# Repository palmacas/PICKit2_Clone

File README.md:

# PICKit2 Clone

This is a DIY version (clone) of the well known Microchip's PICKit2 programmer, with an additional ZIF socket. The repository contains the editable EAGLE files and the scheme on PDF. In addition, the ZIF_Distribution folder contains images with the ICs and jumpers distribution on the ZIF socket depending on the PIC type.

---
More information:  
[PICKit 2 Clone Zócalo ZIF [Spanish]](https://palmacas.com/pickit-2-clone-zocalo-zif/)  
[Zócalo ZIF – PICKit 2 y PICKit 3 [Spanish]](https://palmacas.com/zocalo-zif-pickit-2-y-pickit-3/)  
[Distribución de Zócalo ZIF [Spanish]](https://palmacas.com/distribucion-zocalo-zif/)  
[PICKit 2 Clone ICSP [Spanish]](https://palmacas.com/pickit-2-clone-icsp/)

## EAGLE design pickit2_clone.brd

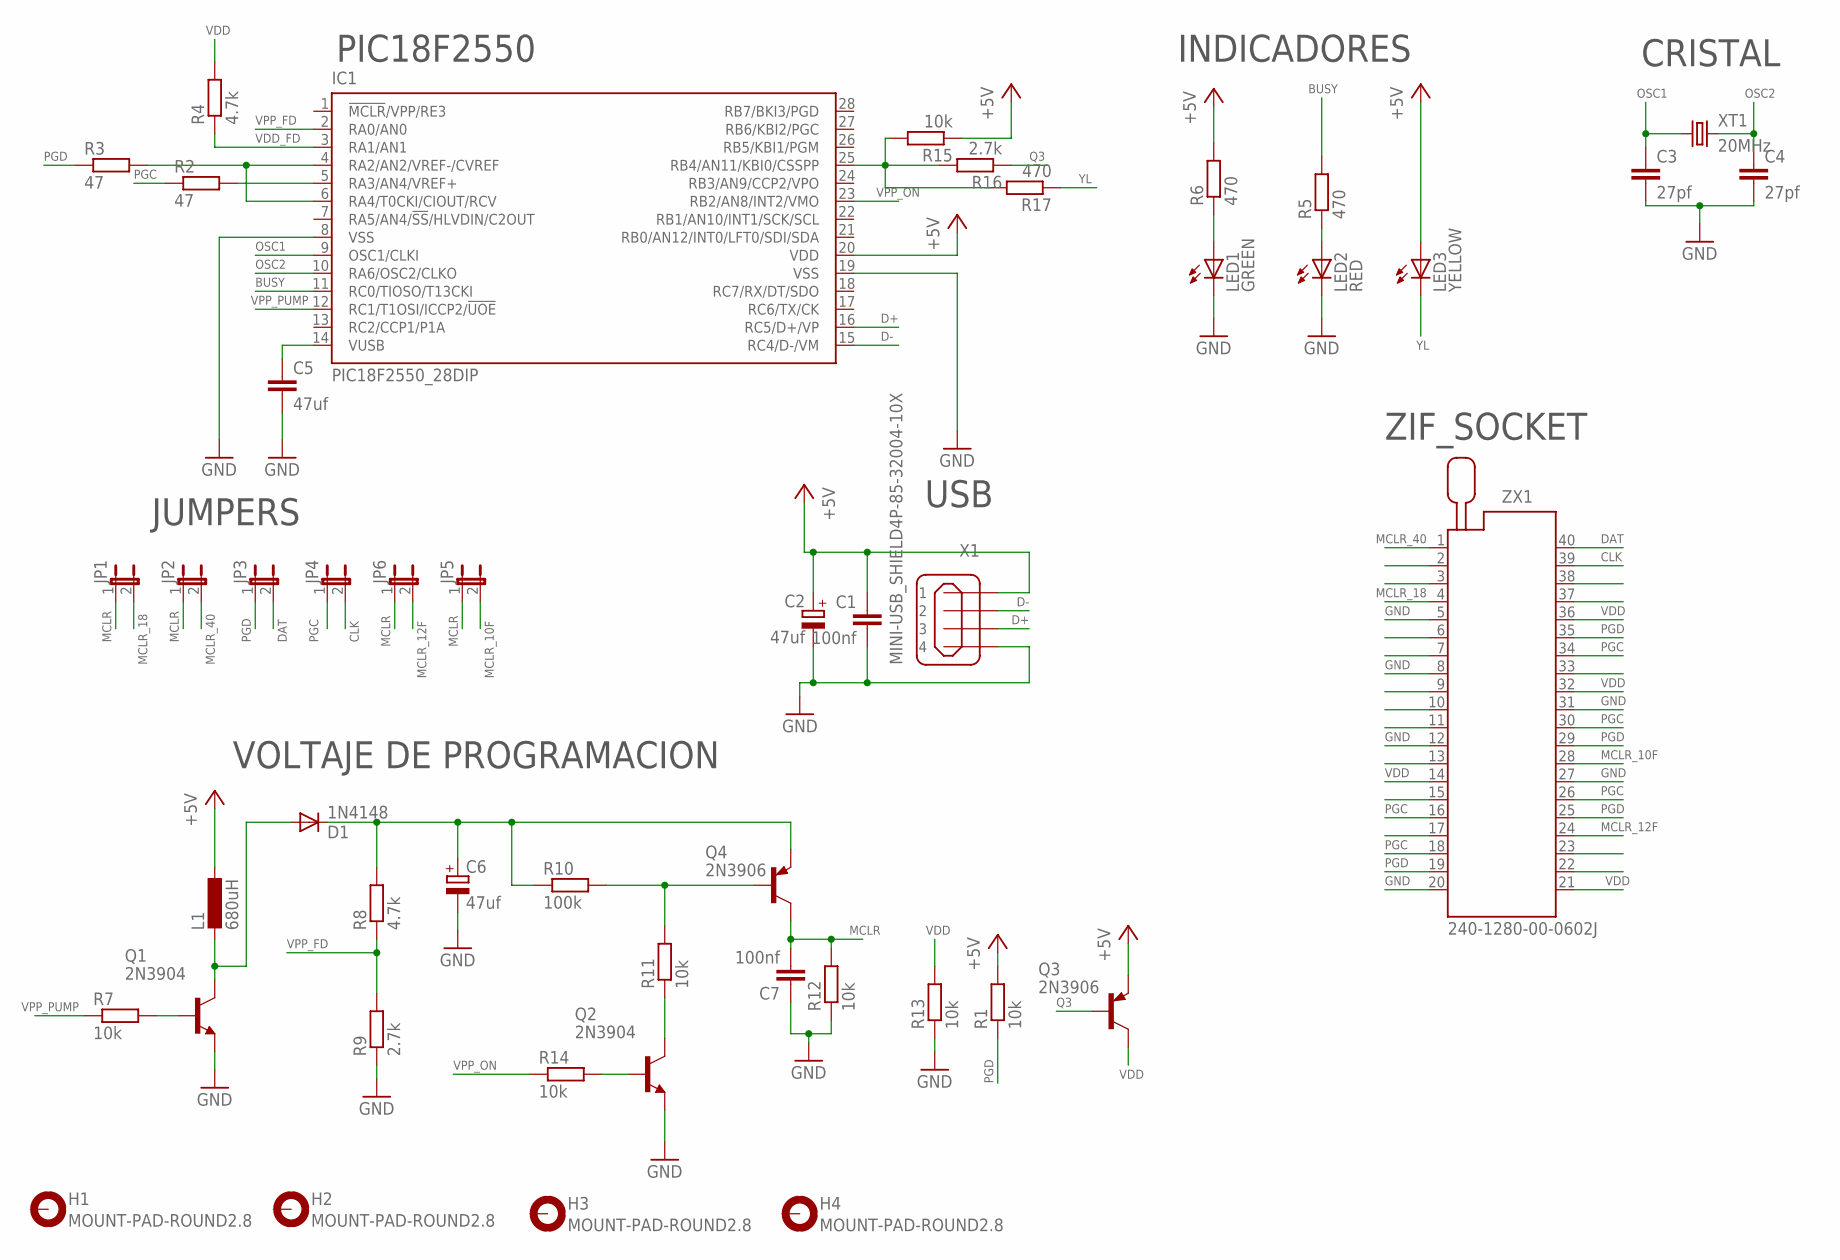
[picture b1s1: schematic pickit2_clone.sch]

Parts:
C1, C7: 100nf; C025-030X050
C2, C6: 47uf; E2-5
C3, C4: 27pf; C050-030X075
C5: 47uf; C050-030X075
D1: 1N4148; DO35-10
H1, H2, H3, H4: MOUNT-PAD-ROUND2.8; 2,8-PAD
IC1: PIC18F2550_28DIP; DIL28-3
JP1, JP2, JP3, JP4, JP5, JP6: JP1E; JP1
L1: 680uH; 0207/10
LED1: GREEN; LED5MM
LED2: RED; LED5MM
LED3: YELLOW; LED5MM
Q1, Q2: 2N3904; TO92-EBC
Q3, Q4: 2N3906; TO92-CBE
R1, R7, R11, R12, R13, R14, R15: 10k; 0207/7
R2, R3: 47; 0207/7
R4, R8: 4.7k; 0207/7
R5, R6, R17: 470; 0207/7
R9, R16: 2.7k; 0207/7
R10: 100k; 0207/7
X1: MINI-USB_SHIELD4P-85-32004-10X; 85-32004-10X
XT1: 20MHz; HC49/S
ZX1: 240-1280-00-0602J

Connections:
+5V: C1.1, C2.+, IC1.20 (VDD), L1.1, LED3.A, Q3.E, R1.2, R6.2, R15.1, X1.1
BUSY: IC1.11 (RC0/TIOSO/T13CKI), R5.2
CLK: JP4.2, ZX1.39
D+: IC1.16 (RC5/D+/VP), X1.3
D-: IC1.15 (RC4/D-/VM), X1.2
DAT: JP3.2, ZX1.40
GND: C1.2, C2.-, C3.2, C4.2, C5.2, C6.-, C7.1, IC1.8 (VSS), IC1.19 (VSS), LED1.K (C), LED2.K (C), Q1.E, Q2.E, R9.1, R12.1, R13.1, X1.4, ZX1.5, ZX1.8, ZX1.12, ZX1.20, ZX1.27, ZX1.31
MCLR: C7.2, JP1.1, JP2.1, JP5.1, JP6.1, Q4.C, R12.2
MCLR_10F: JP5.2, ZX1.28
MCLR_12F: JP6.2, ZX1.24
MCLR_18: JP1.2, ZX1.4
MCLR_40: JP2.2, ZX1.1
unnamed: C5.1, IC1.14 (VUSB)
unnamed: LED1.A, R6.1
unnamed: IC1.4 (RA2/AN2/VREF-/CVREF), IC1.6 (RA4/T0CKI/CIOUT/RCV), R3.2
unnamed: Q1.B, R7.2
unnamed: IC1.5 (RA3/AN4/VREF+), R2.2
unnamed: LED2.A, R5.1
unnamed: C6.+, D1.C, Q4.E, R8.2, R10.1
unnamed: Q4.B, R10.2, R11.2
unnamed: IC1.25 (RB4/AN11/KBI0/CSSPP), R15.2, R16.2, R17.2
unnamed: Q2.C, R11.1
unnamed: Q2.B, R14.2
unnamed: D1.A, L1.2, Q1.C
OSC1: C3.1, IC1.9 (OSC1/CLKI), XT1.1
OSC2: C4.1, IC1.10 (RA6/OSC2/CLKO), XT1.2
PGC: JP4.1, R2.1, ZX1.16, ZX1.18, ZX1.26, ZX1.30, ZX1.34
PGD: JP3.1, R1.1, R3.1, ZX1.19, ZX1.25, ZX1.29, ZX1.35
Q3: Q3.B, R16.1
VDD: Q3.C, R4.2, R13.2, ZX1.14, ZX1.21, ZX1.32, ZX1.36
VDD_FD: IC1.3 (RA1/AN1), R4.1
VPP_FD: IC1.2 (RA0/AN0), R8.1, R9.2
VPP_ON: IC1.23 (RB2/AN8/INT2/VMO), R14.1
VPP_PUMP: IC1.12 (RC1/T1OSI/ICCP2/!UOE), R7.1
YL: LED3.K (C), R17.1

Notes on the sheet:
PIC18F2550
INDICADORES
USB
ZIF_SOCKET
VOLTAJE DE PROGRAMACION
CRISTAL
JUMPERS

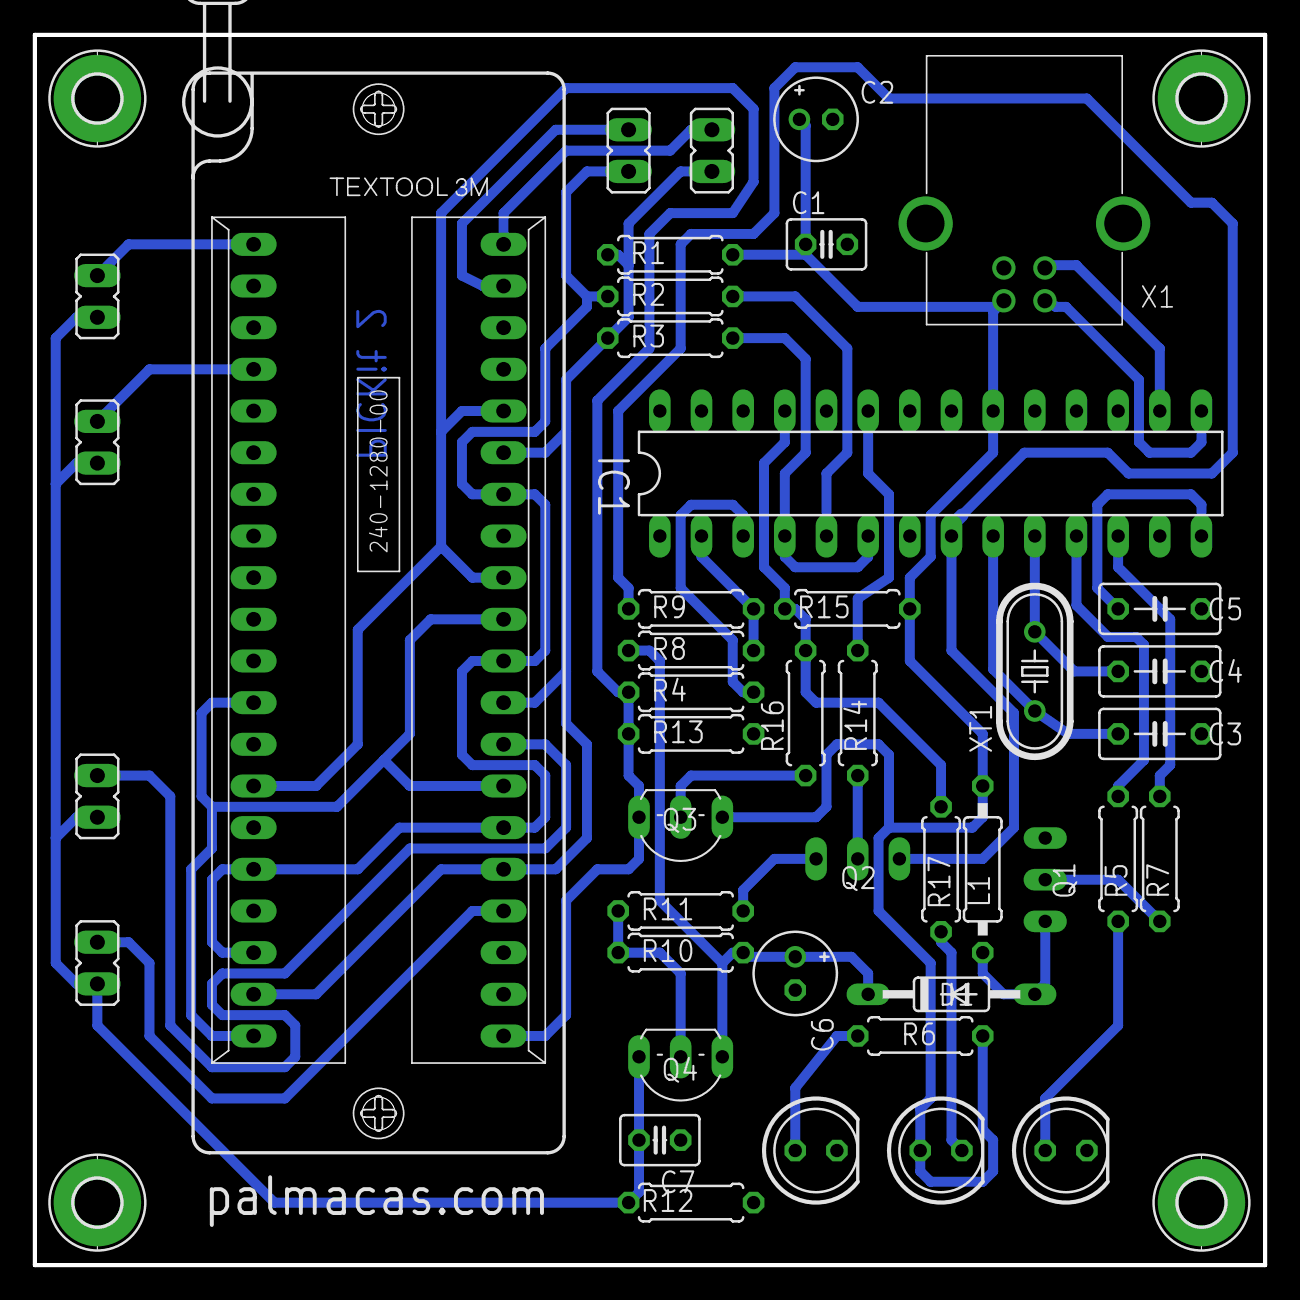
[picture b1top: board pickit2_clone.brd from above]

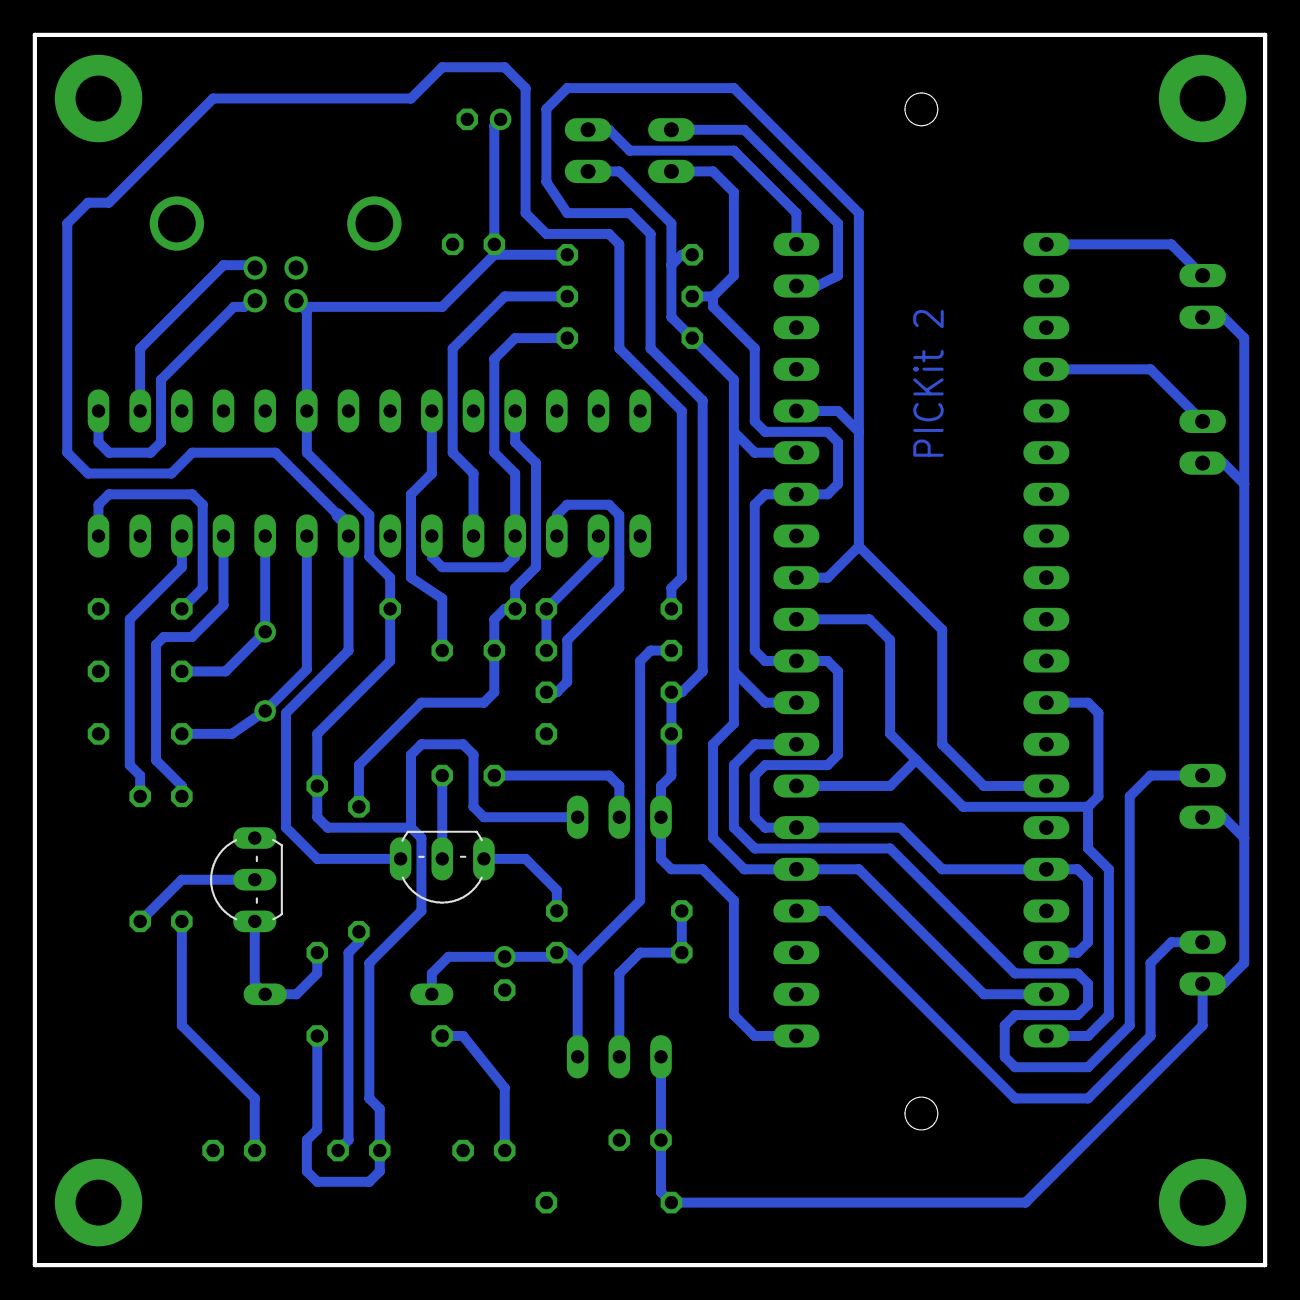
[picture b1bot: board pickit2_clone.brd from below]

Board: 2 copper layers, 75.0 x 75.0 mm, 47 parts (2 on the bottom side), 35 nets.

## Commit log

2020-05-20 Create LICENSE
2020-05-21 ZIF distribution images
2020-06-03 Update LICENSE
